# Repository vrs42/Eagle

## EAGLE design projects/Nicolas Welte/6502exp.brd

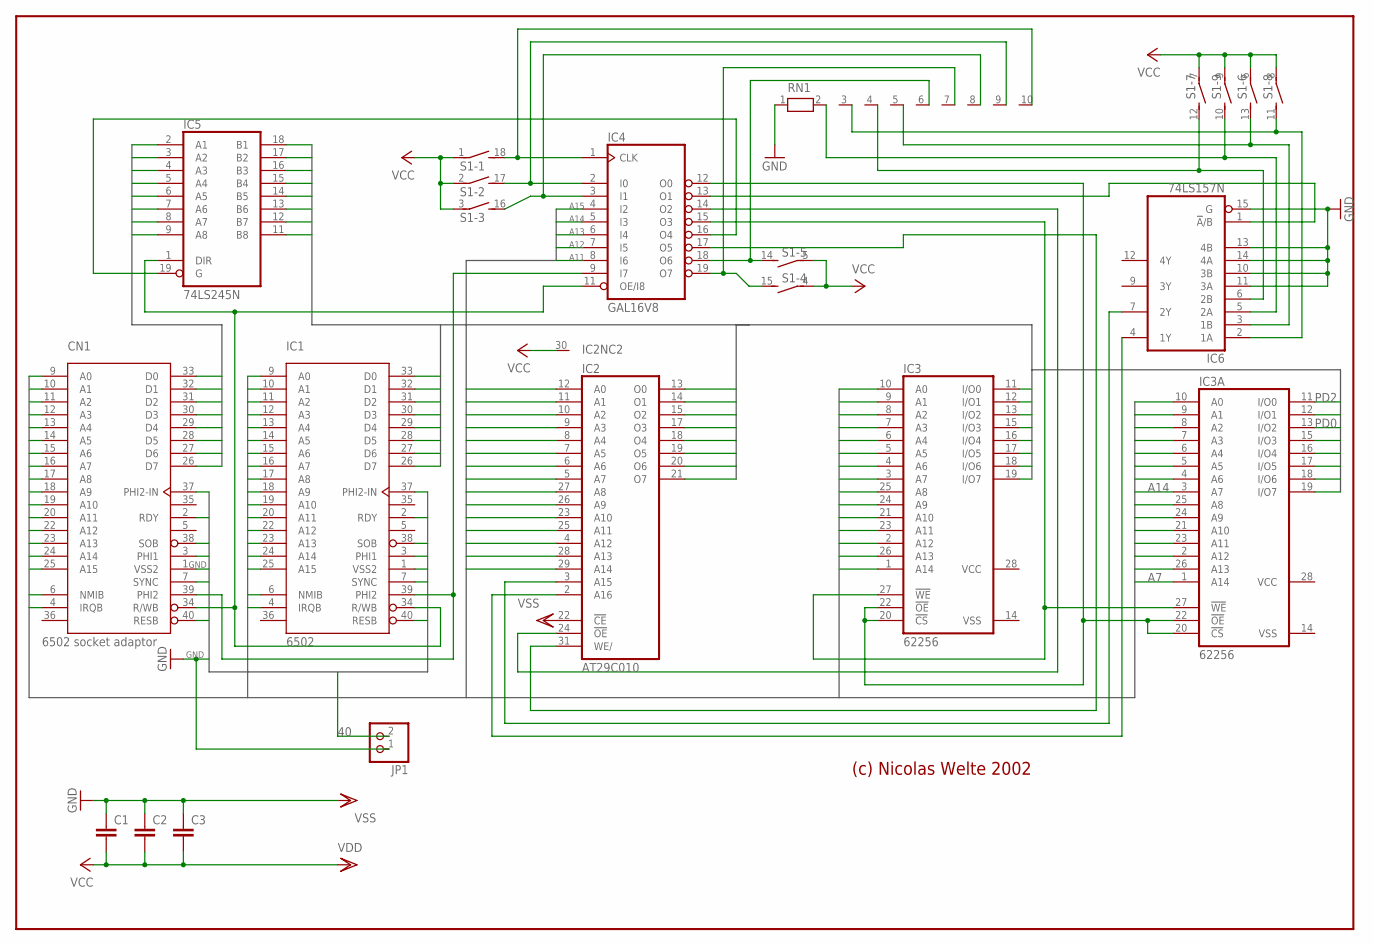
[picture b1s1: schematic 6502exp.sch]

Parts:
C1, C2, C3: C5/3; C5B3
CN1: 6502 socket adaptor; DIP-40
IC1: 6502; DIP-40
IC2: AT29C010; DIL32-3
IC3: 62256; DIL28-6
IC3A: 62256; SO28L
IC4: GAL16V8; DIL20
IC5: 74LS245N; DIL20
IC6: 74LS157N; DIL16
JP1: PINHD-1X2; 1X02
RN1: RN09; RN-10
S1: DS09E; DS-09

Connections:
2: CN1.2 (RDY), IC1.2 (RDY)
3: CN1.3 (PHI1), IC1.3 (PHI1)
7: CN1.7 (SYNC), IC1.7 (SYNC)
37: CN1.37 (PHI2-IN), IC1.37 (PHI2-IN)
38: CN1.38 (SOB), IC1.38 (SOB)
40: CN1.40 (RESB), IC1.40 (RESB), JP1.2
A0: CN1.9 (A0), IC1.9 (A0), IC2.12 (A0), IC3.10 (A0), IC3A.10 (A0)
A1: CN1.10 (A1), IC1.10 (A1), IC2.11 (A1), IC3.9 (A1), IC3A.9 (A1)
A2: CN1.11 (A2), IC1.11 (A2), IC2.10 (A2), IC3.8 (A2), IC3A.8 (A2)
A3: CN1.12 (A3), IC1.12 (A3), IC2.9 (A3), IC3.7 (A3), IC3A.7 (A3)
A4: CN1.13 (A4), IC1.13 (A4), IC2.8 (A4), IC3.6 (A4), IC3A.6 (A4)
A5: CN1.14 (A5), IC1.14 (A5), IC2.7 (A5), IC3.5 (A5), IC3A.5 (A5)
A6: CN1.15 (A6), IC1.15 (A6), IC2.6 (A6), IC3.4 (A6), IC3A.4 (A6)
A7: CN1.16 (A7), IC1.16 (A7), IC2.5 (A7), IC3.3 (A7), IC3A.1 (A14)
A8: CN1.17 (A8), IC1.17 (A8), IC2.27 (A8), IC3.25 (A8), IC3A.25 (A8)
A9: CN1.18 (A9), IC1.18 (A9), IC2.26 (A9), IC3.24 (A9), IC3A.24 (A9)
A10: CN1.19 (A10), IC1.19 (A10), IC2.23 (A10), IC3.21 (A10), IC3A.21 (A10)
A11: CN1.20 (A11), IC1.20 (A11), IC2.25 (A11), IC3.23 (A11), IC3A.23 (A11), IC4.8 (I6)
A12: CN1.22 (A12), IC1.22 (A12), IC2.4 (A12), IC3.2 (A12), IC3A.2 (A12), IC4.7 (I5)
A13: CN1.23 (A13), IC1.23 (A13), IC2.28 (A13), IC3.26 (A13), IC3A.26 (A13), IC4.6 (I4)
A14: CN1.24 (A14), IC1.24 (A14), IC2.29 (A14), IC3.1 (A14), IC3A.3 (A7), IC4.5 (I3)
A15: CN1.25 (A15), IC1.25 (A15), IC4.4 (I2)
D0: CN1.33 (D0), IC5.2 (A1)
D1: CN1.32 (D1), IC5.3 (A2)
D2: CN1.31 (D2), IC5.4 (A3)
D3: CN1.30 (D3), IC5.5 (A4)
D4: CN1.29 (D4), IC5.6 (A5)
D5: CN1.28 (D5), IC5.7 (A6)
D6: CN1.27 (D6), IC5.8 (A7)
D7: CN1.26 (D7), IC5.9 (A8)
GND: C1.1, C2.1, C3.1, CN1.1 (VSS2), CN1.21 (VSS), IC1.1 (VSS2), IC1.21 (VSS), IC2.16 (GND), IC2.22 (!CE), IC3.14 (VSS), IC3A.14 (VSS), IC4.10 (GND), IC5.10 (GND), IC6.8 (GND), IC6.10 (3B), IC6.11 (3A), IC6.13 (4B), IC6.14 (4A), IC6.15 (G), JP1.1, RN1.1
IRQ: CN1.4 (IRQB), IC1.4 (IRQB)
unnamed: CN1.34 (R/WB), IC1.34 (R/WB), IC4.11 (OE/I8), IC5.1 (DIR)
unnamed: IC4.3 (I1), RN1.8, S1.16 (2)
unnamed: CN1.39 (PHI2), IC1.39 (PHI2), IC4.9 (I7)
unnamed: IC4.2 (I0), RN1.9, S1.17 (2)
unnamed: IC4.1 (CLK), RN1.10, S1.18 (2)
unnamed: IC4.18 (O6), RN1.6, S1.14 (2)
unnamed: IC4.19 (O7), RN1.7, S1.15 (2)
unnamed: IC4.16 (O4), IC5.19 (G)
unnamed: IC3.27 (!WE), IC3A.27 (!WE), IC4.15 (O3)
unnamed: IC2.24 (!OE), IC4.14 (O2)
unnamed: IC2.31 (WE/), IC4.17 (O5)
unnamed: IC4.13 (O1), IC6.1 (!A!/B)
unnamed: IC2.3 (A15), IC6.7 (2Y)
unnamed: IC3.20 (!CS), IC3.22 (!OE), IC3A.20 (!CS), IC3A.22 (!OE), IC4.12 (O0)
unnamed: IC2.2 (A16), IC6.4 (1Y)
unnamed: IC6.2 (1A), RN1.3, S1.11 (2)
unnamed: IC6.3 (1B), RN1.5, S1.13 (2)
unnamed: IC6.5 (2A), RN1.2, S1.10 (2)
unnamed: IC6.6 (2B), RN1.4, S1.12 (2)
NMI: CN1.6 (NMIB), IC1.6 (NMIB)
PD0: IC1.33 (D0), IC2.13 (O0), IC3.11 (I/O0), IC3A.13 (I/O2), IC5.18 (B1)
PD1: IC1.32 (D1), IC2.14 (O1), IC3.12 (I/O1), IC3A.12 (I/O1), IC5.17 (B2)
PD2: IC1.31 (D2), IC2.15 (O2), IC3.13 (I/O2), IC3A.11 (I/O0), IC5.16 (B3)
PD3: IC1.30 (D3), IC2.17 (O3), IC3.15 (I/O3), IC3A.15 (I/O3), IC5.15 (B4)
PD4: IC1.29 (D4), IC2.18 (O4), IC3.16 (I/O4), IC3A.16 (I/O4), IC5.14 (B5)
PD5: IC1.28 (D5), IC2.19 (O5), IC3.17 (I/O5), IC3A.17 (I/O5), IC5.13 (B6)
PD6: IC1.27 (D6), IC2.20 (O6), IC3.18 (I/O6), IC3A.18 (I/O6), IC5.12 (B7)
PD7: IC1.26 (D7), IC2.21 (O7), IC3.19 (I/O7), IC3A.19 (I/O7), IC5.11 (B8)
VCC: C1.2, C2.2, C3.2, CN1.8 (VDD), IC1.8 (VDD), IC2.30 (NC), IC2.32 (VCC), IC3.28 (VCC), IC3A.28 (VCC), IC4.20 (VCC), IC5.20 (VCC), IC6.16 (VCC), S1.1, S1.2 (1), S1.3 (1), S1.4 (1), S1.5 (1), S1.6 (1), S1.7 (1), S1.8 (1), S1.9 (1)

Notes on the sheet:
(c) Nicolas Welte 2002

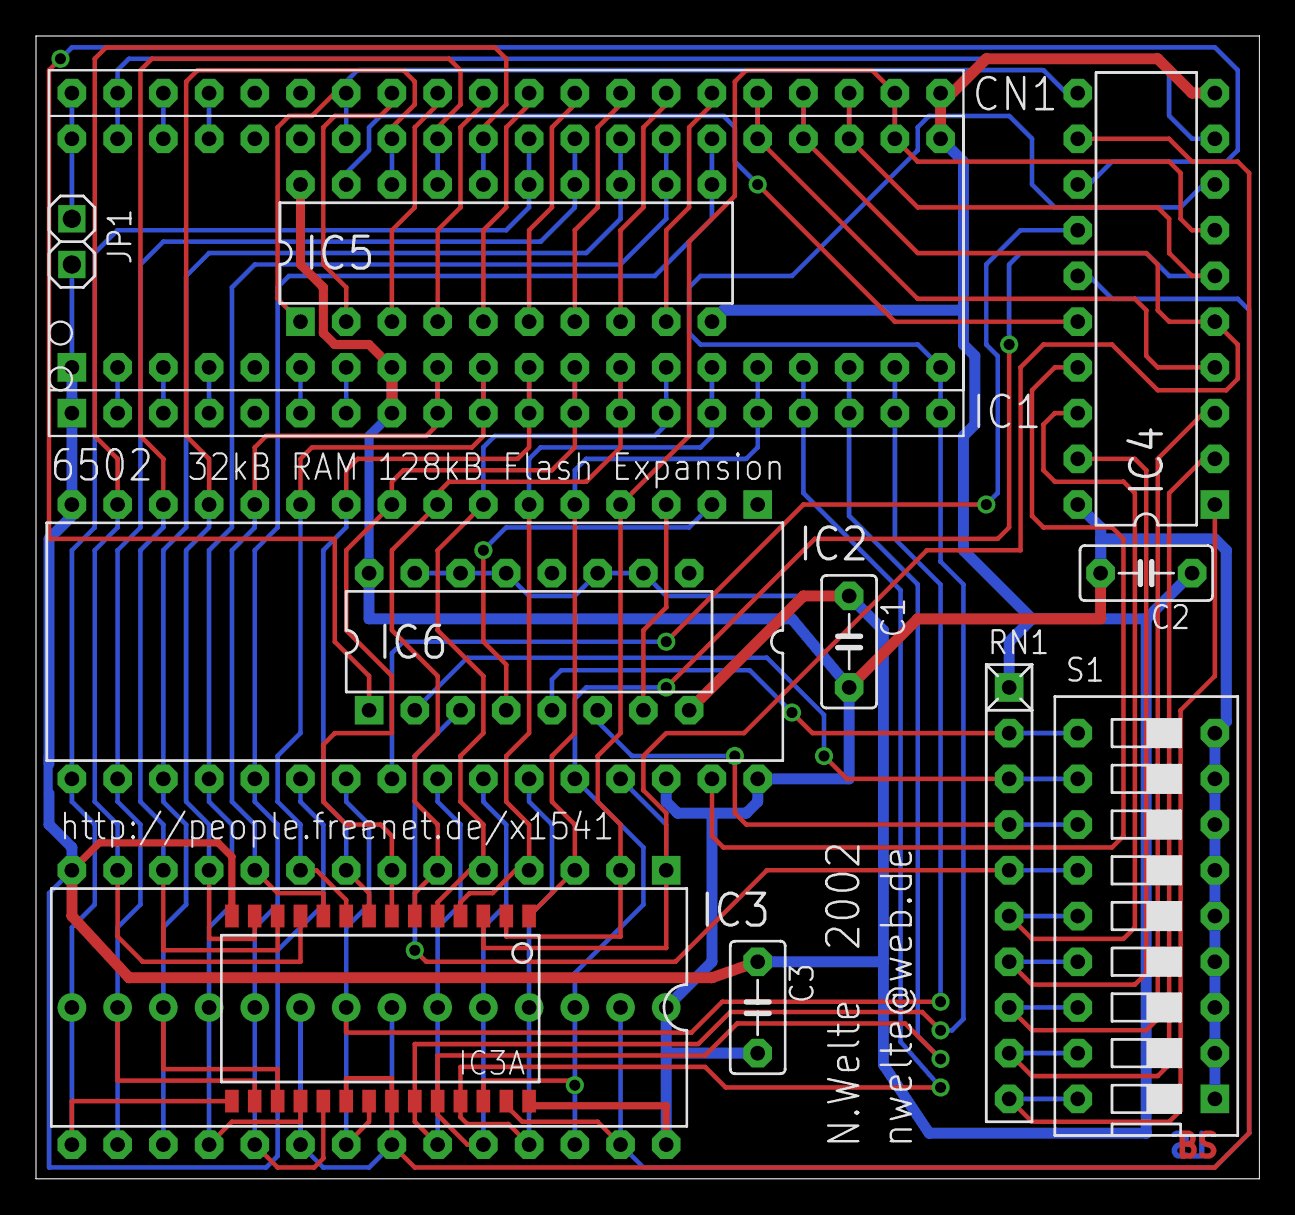
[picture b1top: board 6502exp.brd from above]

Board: 2 copper layers, 68.0 x 63.5 mm, 14 parts (0 on the bottom side), 61 nets.

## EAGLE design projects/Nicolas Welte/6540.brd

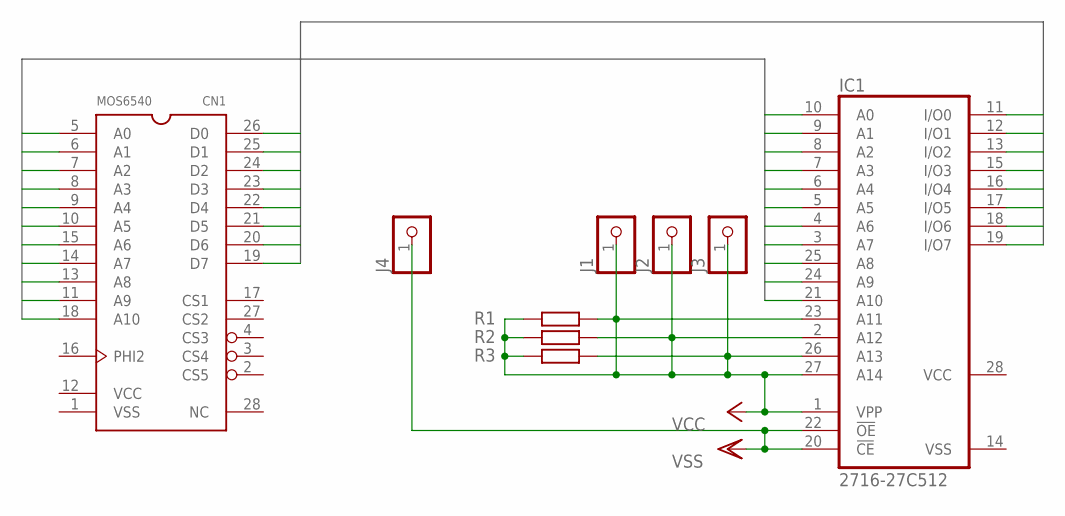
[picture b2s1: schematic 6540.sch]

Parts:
CN1: MOS6540; DIP-28
IC1: 2716-27C512; DIL28-6
J1, J2, J3, J4: PINHD-1X1; 1X01
R1, R2, R3: R-EU_M0805; M0805

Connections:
A0: CN1.5 (A0), IC1.10 (A0)
A1: CN1.6 (A1), IC1.9 (A1)
A2: CN1.7 (A2), IC1.8 (A2)
A3: CN1.8 (A3), IC1.7 (A3)
A4: CN1.9 (A4), IC1.6 (A4)
A5: CN1.10 (A5), IC1.5 (A5)
A6: CN1.15 (A6), IC1.4 (A6)
A7: CN1.14 (A7), IC1.3 (A7)
A8: CN1.13 (A8), IC1.25 (A8)
A9: CN1.11 (A9), IC1.24 (A9)
A10: CN1.18 (A10), IC1.21 (A10)
D0: CN1.26 (D0), IC1.11 (I/O0)
D1: CN1.25 (D1), IC1.12 (I/O1)
D2: CN1.24 (D2), IC1.13 (I/O2)
D3: CN1.23 (D3), IC1.15 (I/O3)
D4: CN1.22 (D4), IC1.16 (I/O4)
D5: CN1.21 (D5), IC1.17 (I/O5)
D6: CN1.20 (D6), IC1.18 (I/O6)
D7: CN1.19 (D7), IC1.19 (I/O7)
VCC: CN1.12 (VCC), IC1.1 (VPP), IC1.2 (A12), IC1.23 (A11), IC1.26 (A13), IC1.27 (A14), IC1.28 (VCC), J1.1, J2.1, J3.1, R1.1, R1.2, R2.1, R2.2, R3.1, R3.2
VSS: CN1.1 (VSS), IC1.14 (VSS), IC1.20 (!CE), IC1.22 (!OE), J4.1

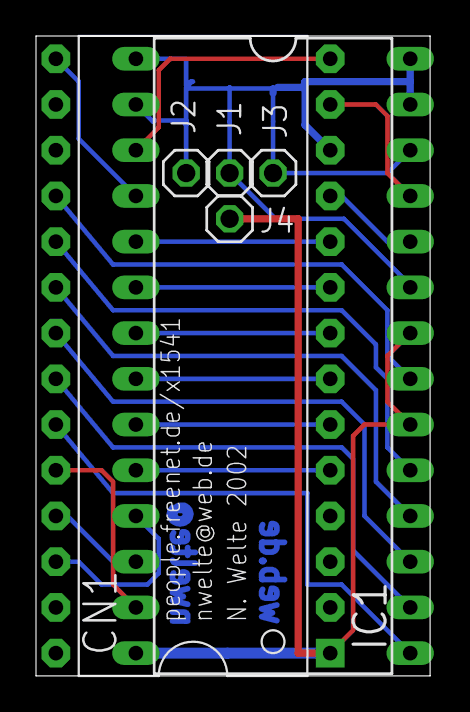
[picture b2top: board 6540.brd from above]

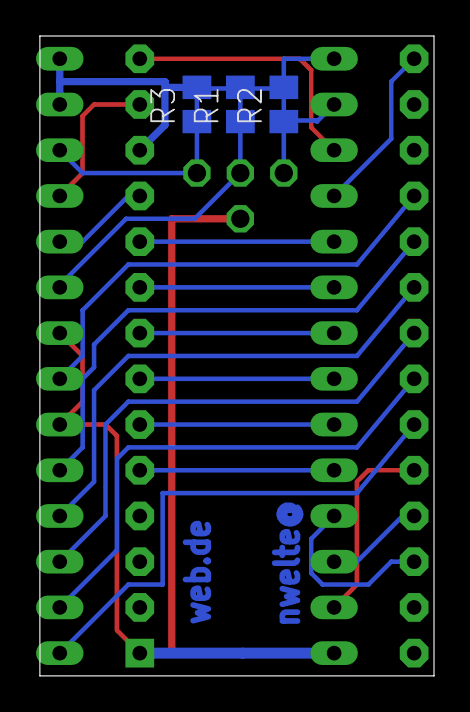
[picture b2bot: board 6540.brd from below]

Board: 2 copper layers, 21.9 x 35.5 mm, 9 parts (3 on the bottom side), 21 nets.

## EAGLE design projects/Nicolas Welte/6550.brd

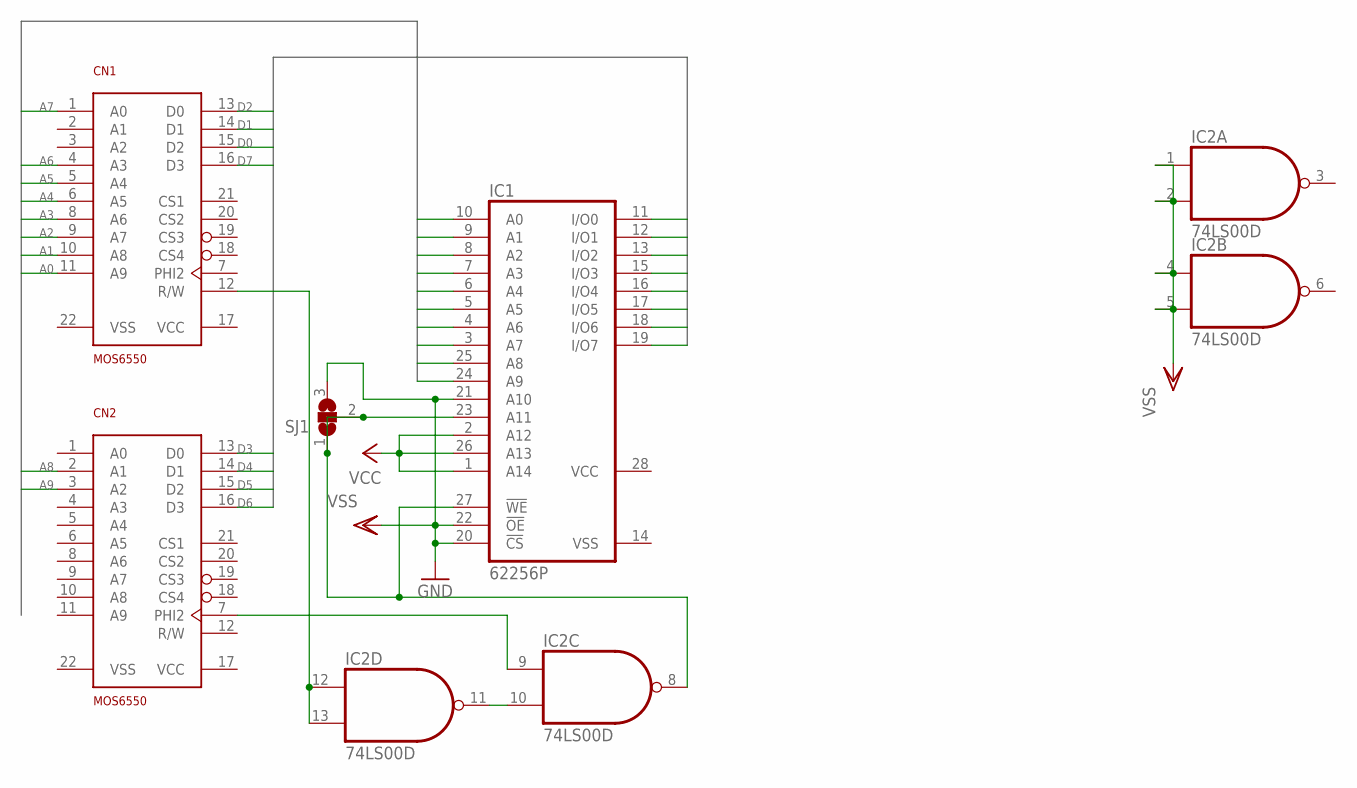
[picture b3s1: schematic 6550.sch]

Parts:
CN1, CN2: MOS6550; DIP-22
IC1: 62256P; DIL28-6
IC2: 74LS00D; SO14
SJ1: SJ2W; SJ_2

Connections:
A0: CN1.11 (A9), IC1.10 (A0)
A1: CN1.10 (A8), IC1.9 (A1)
A2: CN1.9 (A7), IC1.8 (A2)
A3: CN1.8 (A6), IC1.7 (A3)
A4: CN1.6 (A5), IC1.6 (A4)
A5: CN1.5 (A4), IC1.5 (A5)
A6: CN1.4 (A3), IC1.4 (A6)
A7: CN1.1 (A0), IC1.3 (A7)
A8: CN2.2 (A1), IC1.25 (A8)
A9: CN2.3 (A2), IC1.24 (A9)
D0: CN1.15 (D2), IC1.11 (I/O0)
D1: CN1.14 (D1), IC1.12 (I/O1)
D2: CN1.13 (D0), IC1.13 (I/O2)
D3: CN2.13 (D0), IC1.15 (I/O3)
D4: CN2.14 (D1), IC1.16 (I/O4)
D5: CN2.15 (D2), IC1.17 (I/O5)
D6: CN2.16 (D3), IC1.18 (I/O6)
D7: CN1.16 (D3), IC1.19 (I/O7)
unnamed: CN1.12 (R/W), IC2.12 (I0), IC2.13 (I1)
unnamed: IC2.10 (I1), IC2.11 (O)
unnamed: CN2.7 (PHI2), IC2.9 (I0)
unnamed: IC1.23 (A11), IC1.27 (!WE), IC2.8 (O), SJ1.1, SJ1.2
VCC: CN1.17 (VCC), CN2.17 (VCC), IC1.1 (A14), IC1.2 (A12), IC1.26 (A13), IC1.28 (VCC), IC2.14 (VCC)
VSS: CN1.22 (VSS), CN2.22 (VSS), IC1.14 (VSS), IC1.20 (!CS), IC1.21 (A10), IC1.22 (!OE), IC2.1 (I0), IC2.2 (I1), IC2.4 (I0), IC2.5 (I1), IC2.7 (GND), SJ1.3

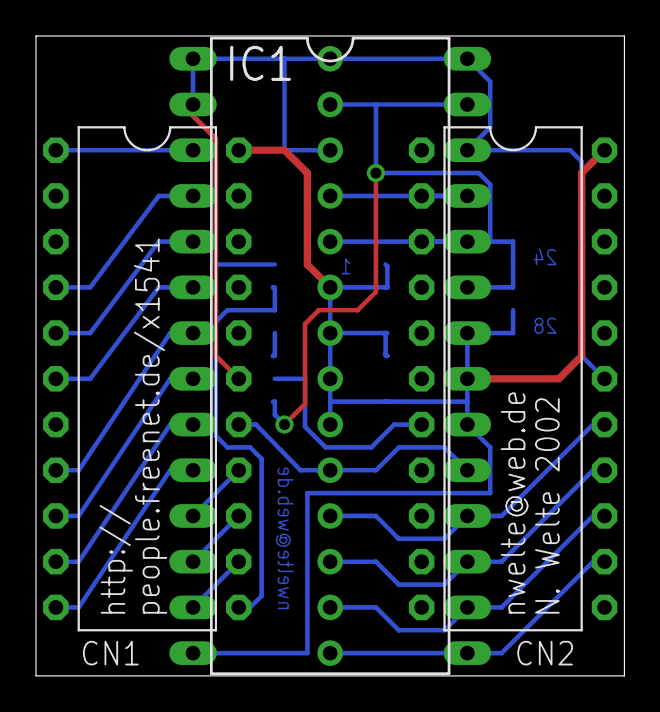
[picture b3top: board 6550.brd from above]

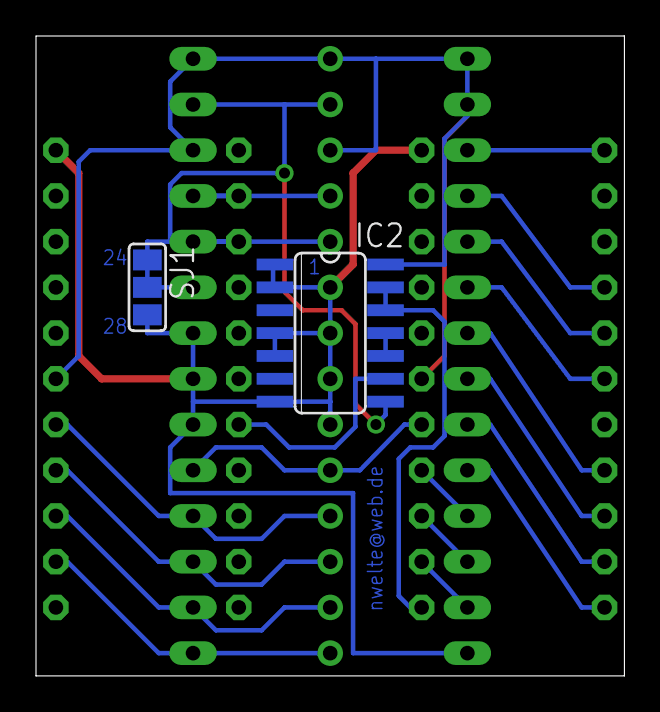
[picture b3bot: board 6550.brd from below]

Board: 2 copper layers, 32.7 x 35.5 mm, 5 parts (2 on the bottom side), 24 nets.

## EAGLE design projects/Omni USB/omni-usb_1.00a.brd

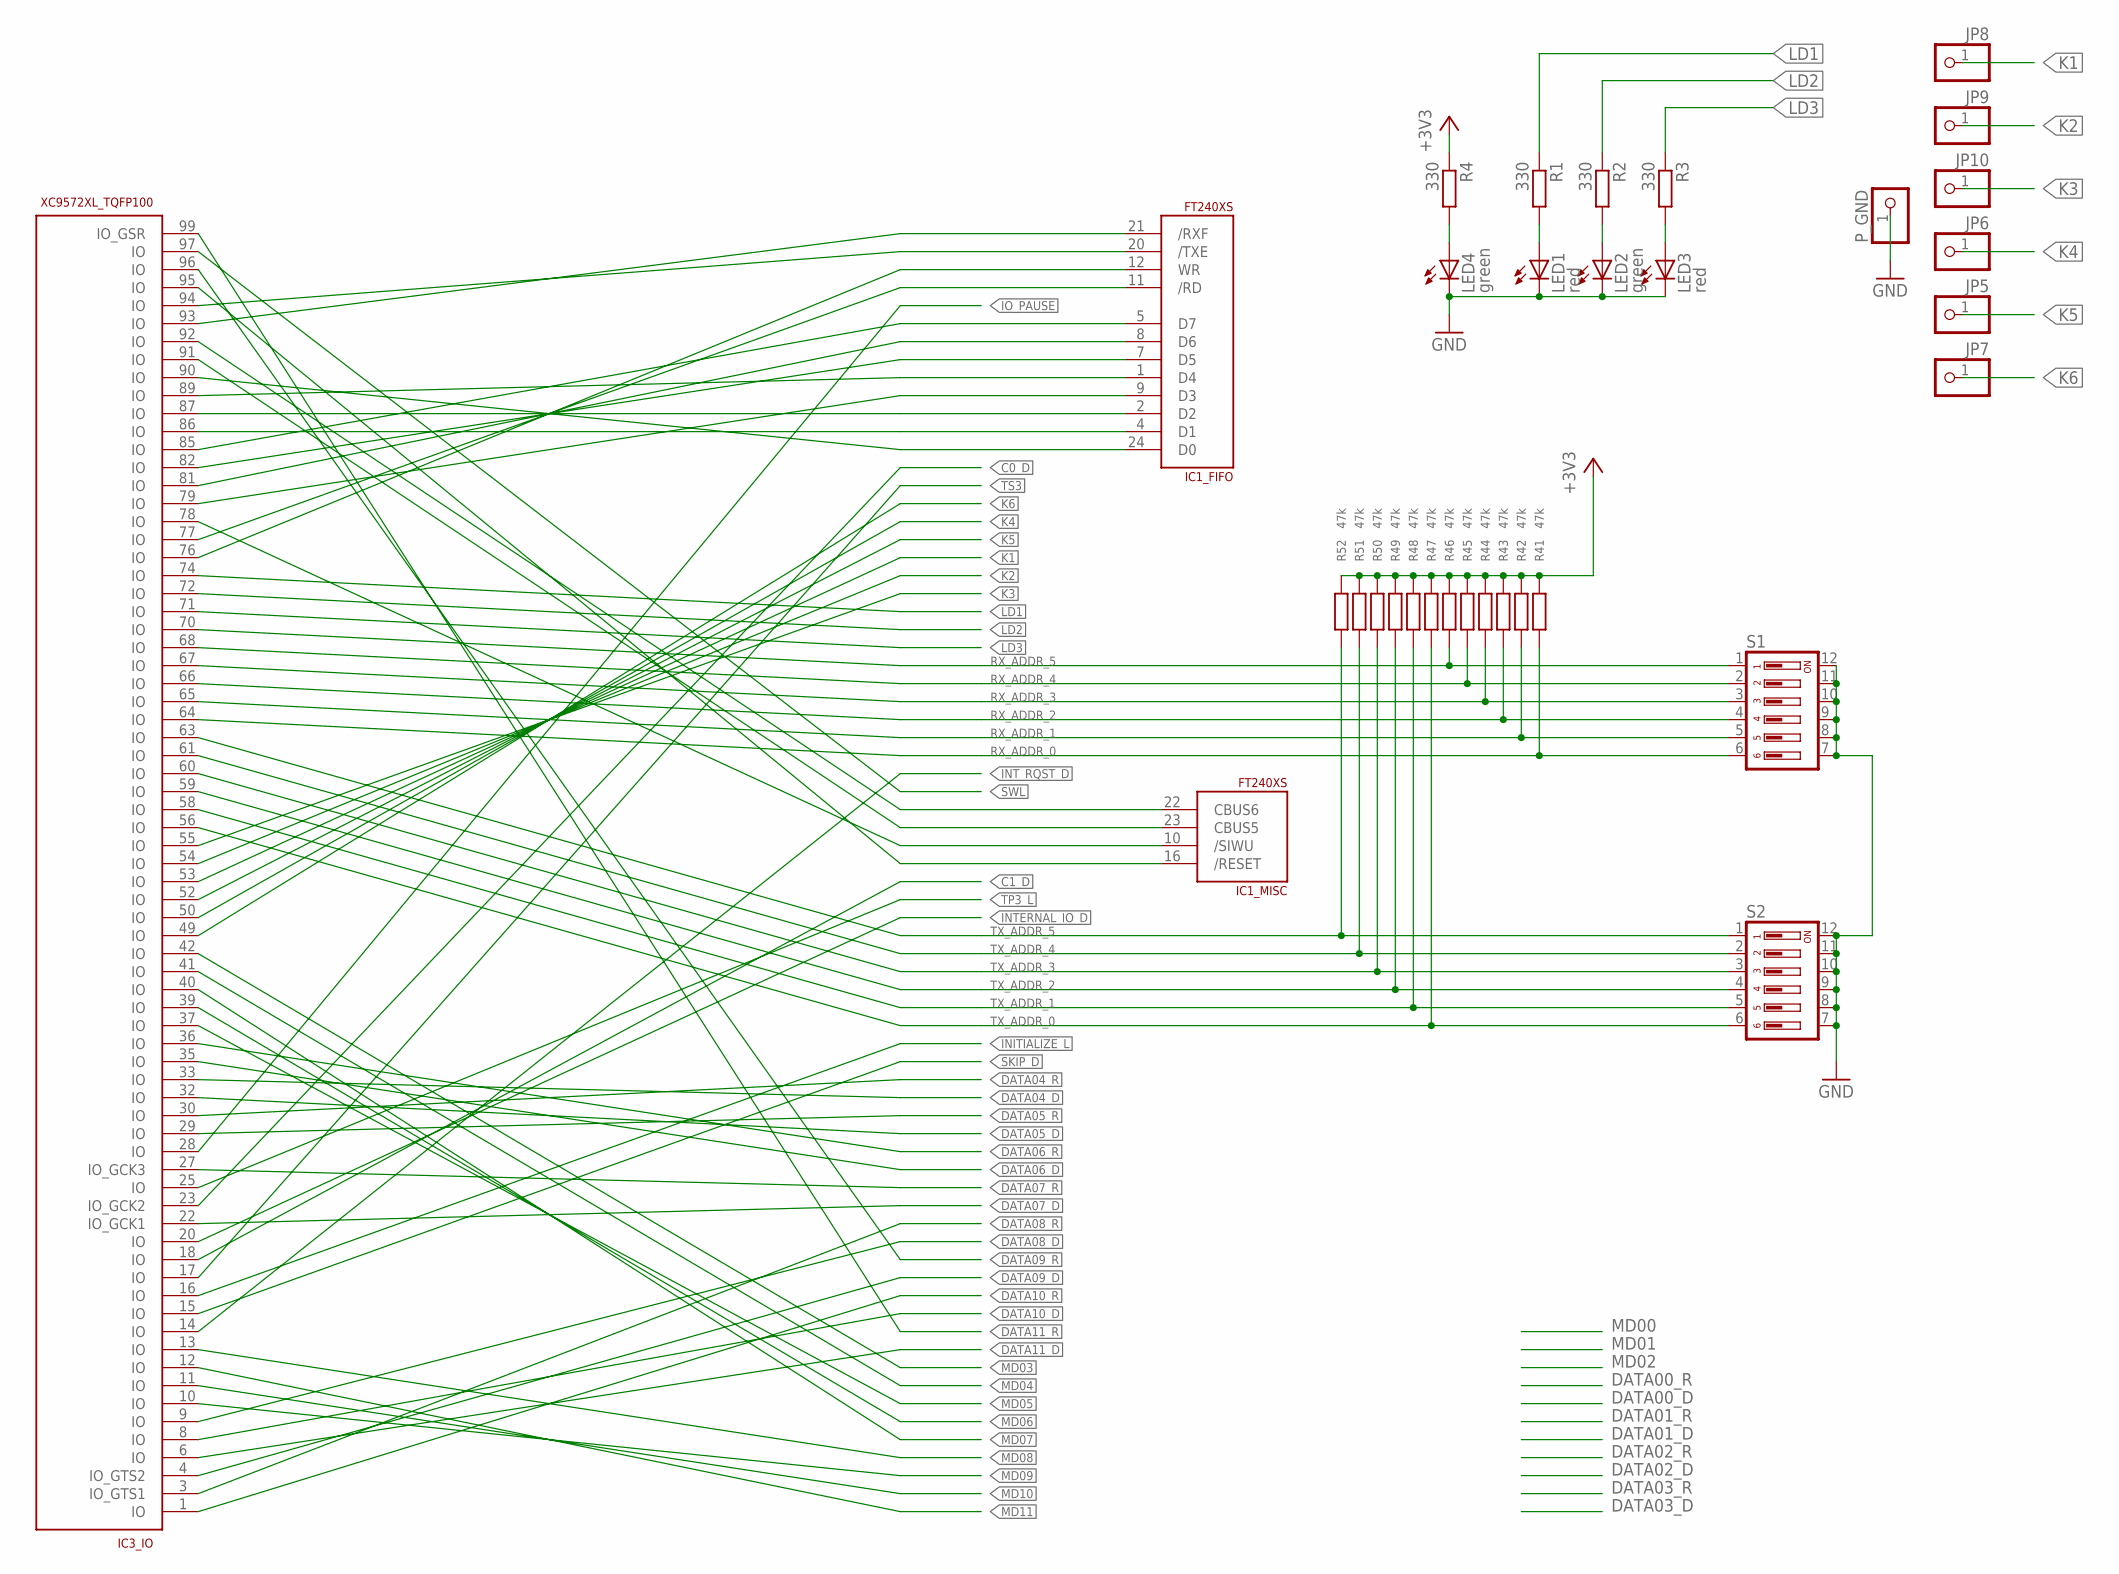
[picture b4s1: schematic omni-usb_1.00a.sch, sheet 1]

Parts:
IC1: FT240XS; TSSOP24; MPN FT240XS
IC3: XC9572XL_TQFP100; TQ100; MPN XC9572XL-10TQG100C
JP5, JP6, JP7, JP8, JP9, JP10: PINHD-1X1; 1X01
LED1, LED3: red; CHIPLED_0805; MPN KP-2012SRC-PRV
LED2, LED4: green; CHIPLED_0805; MPN KPT-2012CGCK
P_GND: PINHD-1X1; 1X01
R1, R2, R3, R4: 330; R0805
R41, R42, R43, R44, R45, R46, R47, R48, R49, R50, R51, R52: 47k; R0805; MPN ERJ6GEYJ473V
S1, S2: DIP06YL

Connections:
!RD: IC1.11 (/RD), IC3.77 (IO)
!RESET: IC1.16 (/RESET), IC3.95 (IO)
!RXF: IC1.21 (/RXF), IC3.93 (IO)
!TXE: IC1.20 (/TXE), IC3.94 (IO)
+3V3: R4.1, R41.2, R42.2, R43.2, R44.2, R45.2, R46.2, R47.2, R48.2, R49.2, R50.2, R51.2, R52.2; also elsewhere on the board
/SIWU: IC1.10 (/SIWU), IC3.78 (IO)
C0_D: IC3.23 (IO_GCK2); also elsewhere on the board
C1_D: IC3.18 (IO); also elsewhere on the board
CBUS5: IC1.23 (CBUS5), IC3.91 (IO)
CBUS6: IC1.22 (CBUS6), IC3.92 (IO)
D0: IC1.24 (D0), IC3.90 (IO)
D1: IC1.4 (D1), IC3.86 (IO)
D2: IC1.2 (D2), IC3.87 (IO)
D3: IC1.9 (D3), IC3.79 (IO)
D4: IC1.1 (D4), IC3.89 (IO)
D5: IC1.7 (D5), IC3.82 (IO)
D6: IC1.8 (D6), IC3.81 (IO)
D7: IC1.5 (D7), IC3.85 (IO)
DATA04_D: IC3.33 (IO); also elsewhere on the board
DATA04_R: IC3.30 (IO); also elsewhere on the board
DATA05_D: IC3.32 (IO); also elsewhere on the board
DATA05_R: IC3.29 (IO); also elsewhere on the board
DATA06_D: IC3.35 (IO); also elsewhere on the board
DATA06_R: IC3.36 (IO); also elsewhere on the board
DATA07_D: IC3.22 (IO_GCK1); also elsewhere on the board
DATA07_R: IC3.27 (IO_GCK3); also elsewhere on the board
DATA08_D: IC3.9 (IO); also elsewhere on the board
DATA08_R: IC3.3 (IO_GTS1); also elsewhere on the board
DATA09_D: IC3.4 (IO_GTS2); also elsewhere on the board
DATA09_R: IC3.96 (IO); also elsewhere on the board
DATA10_D: IC3.8 (IO); also elsewhere on the board
DATA10_R: IC3.1 (IO); also elsewhere on the board
DATA11_D: IC3.6 (IO); also elsewhere on the board
DATA11_R: IC3.99 (IO_GSR); also elsewhere on the board
GND: LED1.C, LED2.C, LED3.C, LED4.C, P_GND.1, S1.7, S1.8, S1.9, S1.10, S1.11, S1.12, S2.7, S2.8, S2.9, S2.10, S2.11, S2.12; also elsewhere on the board
INITIALIZE_L: IC3.16 (IO); also elsewhere on the board
INTERNAL_IO_D: IC3.20 (IO); also elsewhere on the board
INT_RQST_D: IC3.14 (IO); also elsewhere on the board
IO_PAUSE: IC3.28 (IO); also elsewhere on the board
K1: IC3.53 (IO), JP8.1
K2: IC3.54 (IO), JP9.1
K3: IC3.55 (IO), JP10.1
K4: IC3.50 (IO), JP6.1
K5: IC3.52 (IO), JP5.1
K6: IC3.49 (IO), JP7.1
LD1: IC3.74 (IO), R1.1
LD2: IC3.72 (IO), R2.1
LD3: IC3.71 (IO), R3.1
LED3: LED2.A, R2.2
MD03: IC3.42 (IO); also elsewhere on the board
MD04: IC3.41 (IO); also elsewhere on the board
MD05: IC3.37 (IO); also elsewhere on the board
MD06: IC3.39 (IO); also elsewhere on the board
MD07: IC3.40 (IO); also elsewhere on the board
MD08: IC3.13 (IO); also elsewhere on the board
MD09: IC3.10 (IO); also elsewhere on the board
MD10: IC3.11 (IO); also elsewhere on the board
MD11: IC3.12 (IO); also elsewhere on the board
unnamed: IC1.12 (WR), IC3.76 (IO)
unnamed: LED1.A, R1.2
unnamed: LED4.A, R4.2
unnamed: LED3.A, R3.2
RX_ADDR_0: IC3.64 (IO), R41.1, S1.6
RX_ADDR_1: IC3.65 (IO), R42.1, S1.5
RX_ADDR_2: IC3.66 (IO), R43.1, S1.4
RX_ADDR_3: IC3.67 (IO), R44.1, S1.3
RX_ADDR_4: IC3.68 (IO), R45.1, S1.2
RX_ADDR_5: IC3.70 (IO), R46.1, S1.1
SKIP_D: IC3.15 (IO); also elsewhere on the board
SWL: IC3.97 (IO); also elsewhere on the board
TP3_L: IC3.25 (IO); also elsewhere on the board
TS3: IC3.17 (IO); also elsewhere on the board
TX_ADDR_0: IC3.56 (IO), R47.1, S2.6
TX_ADDR_1: IC3.58 (IO), R48.1, S2.5
TX_ADDR_2: IC3.59 (IO), R49.1, S2.4
TX_ADDR_3: IC3.60 (IO), R50.1, S2.3
TX_ADDR_4: IC3.61 (IO), R51.1, S2.2
TX_ADDR_5: IC3.63 (IO), R52.1, S2.1

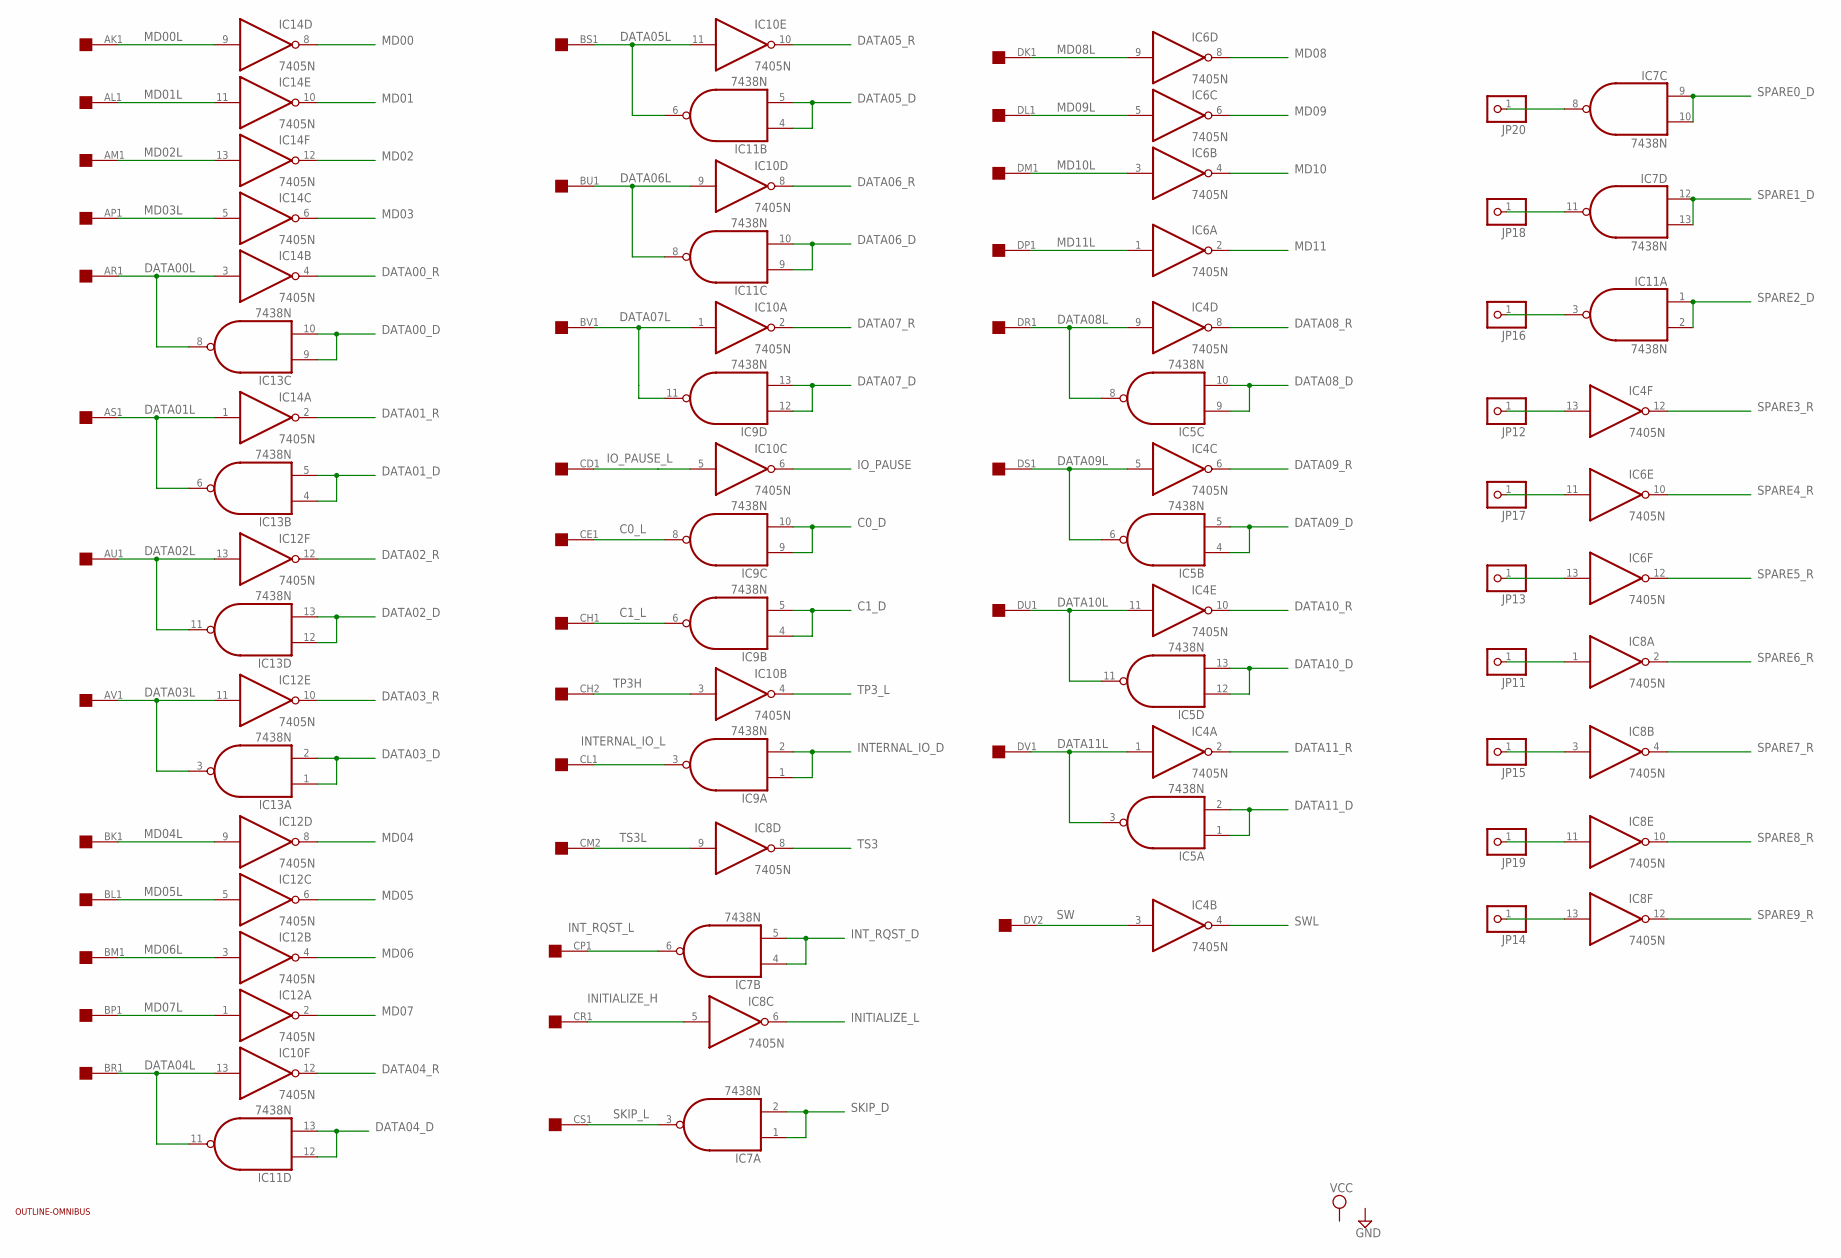
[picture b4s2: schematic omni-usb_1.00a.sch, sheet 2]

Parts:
IC4, IC6, IC8, IC10, IC12, IC14: 7405N; DIL14; MPN SN74AHC05N
IC5, IC7, IC9, IC11, IC13: 7438N; DIL14; MPN SN7438N
JP11, JP12, JP13, JP14, JP15, JP16, JP17, JP18, JP19, JP20: PINHD-1X1; 1X01
U$1: OUTLINE-OMNIBUS; OMNIBUS
U$2: QUAD; EDGE-CON8

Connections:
C0_D: IC9.9 (I0), IC9.10 (I1); also elsewhere on the board
C0_L: IC9.8 (O), U$2.CE1
C1_D: IC9.4 (I0), IC9.5 (I1); also elsewhere on the board
C1_L: IC9.6 (O), U$2.CH1
DATA00L: IC13.8 (O), IC14.3 (I), U$2.AR1
DATA00_D: IC13.9 (I0), IC13.10 (I1)
DATA00_R: IC14.4 (O); also elsewhere on the board
DATA01L: IC13.6 (O), IC14.1 (I), U$2.AS1
DATA01_D: IC13.4 (I0), IC13.5 (I1)
DATA01_R: IC14.2 (O); also elsewhere on the board
DATA02L: IC12.13 (I), IC13.11 (O), U$2.AU1
DATA02_D: IC13.12 (I0), IC13.13 (I1)
DATA02_R: IC12.12 (O); also elsewhere on the board
DATA03L: IC12.11 (I), IC13.3 (O), U$2.AV1
DATA03_D: IC13.1 (I0), IC13.2 (I1)
DATA03_R: IC12.10 (O); also elsewhere on the board
DATA04L: IC10.13 (I), IC11.11 (O), U$2.BR1
DATA04_D: IC11.12 (I0), IC11.13 (I1); also elsewhere on the board
DATA04_R: IC10.12 (O); also elsewhere on the board
DATA05L: IC10.11 (I), IC11.6 (O), U$2.BS1
DATA05_D: IC11.4 (I0), IC11.5 (I1); also elsewhere on the board
DATA05_R: IC10.10 (O); also elsewhere on the board
DATA06L: IC10.9 (I), IC11.8 (O), U$2.BU1
DATA06_D: IC11.9 (I0), IC11.10 (I1); also elsewhere on the board
DATA06_R: IC10.8 (O); also elsewhere on the board
DATA07L: IC9.11 (O), IC10.1 (I), U$2.BV1
DATA07_D: IC9.12 (I0), IC9.13 (I1); also elsewhere on the board
DATA07_R: IC10.2 (O); also elsewhere on the board
DATA08L: IC4.9 (I), IC5.8 (O), U$2.DR1
DATA08_D: IC5.9 (I0), IC5.10 (I1); also elsewhere on the board
DATA08_R: IC4.8 (O); also elsewhere on the board
DATA09L: IC4.5 (I), IC5.6 (O), U$2.DS1
DATA09_D: IC5.4 (I0), IC5.5 (I1); also elsewhere on the board
DATA09_R: IC4.6 (O); also elsewhere on the board
DATA10L: IC4.11 (I), IC5.11 (O), U$2.DU1
DATA10_D: IC5.12 (I0), IC5.13 (I1); also elsewhere on the board
DATA10_R: IC4.10 (O); also elsewhere on the board
DATA11L: IC4.1 (I), IC5.3 (O), U$2.DV1
DATA11_D: IC5.1 (I0), IC5.2 (I1); also elsewhere on the board
DATA11_R: IC4.2 (O); also elsewhere on the board
GND: IC4.7 (GND), IC5.7 (GND), IC6.7 (GND), IC7.7 (GND), IC8.7 (GND), IC9.7 (GND), IC10.7 (GND), IC11.7 (GND), IC12.7 (GND), IC13.7 (GND), IC14.7 (GND); also elsewhere on the board
INITIALIZE_H: IC8.5 (I), U$2.CR1
INITIALIZE_L: IC8.6 (O); also elsewhere on the board
INTERNAL_IO_D: IC9.1 (I0), IC9.2 (I1); also elsewhere on the board
INTERNAL_IO_L: IC9.3 (O), U$2.CL1
INT_RQST_D: IC7.4 (I0), IC7.5 (I1); also elsewhere on the board
INT_RQST_L: IC7.6 (O), U$2.CP1
IO_PAUSE: IC10.6 (O); also elsewhere on the board
IO_PAUSE_L: IC10.5 (I), U$2.CD1
MD00: IC14.8 (O); also elsewhere on the board
MD00L: IC14.9 (I), U$2.AK1
MD01: IC14.10 (O); also elsewhere on the board
MD01L: IC14.11 (I), U$2.AL1
MD02: IC14.12 (O); also elsewhere on the board
MD02L: IC14.13 (I), U$2.AM1
MD03: IC14.6 (O); also elsewhere on the board
MD03L: IC14.5 (I), U$2.AP1
MD04: IC12.8 (O); also elsewhere on the board
MD04L: IC12.9 (I), U$2.BK1
MD05: IC12.6 (O); also elsewhere on the board
MD05L: IC12.5 (I), U$2.BL1
MD06: IC12.4 (O); also elsewhere on the board
MD06L: IC12.3 (I), U$2.BM1
MD07: IC12.2 (O); also elsewhere on the board
MD07L: IC12.1 (I), U$2.BP1
MD08: IC6.8 (O); also elsewhere on the board
MD08L: IC6.9 (I), U$2.DK1
MD09: IC6.6 (O); also elsewhere on the board
MD09L: IC6.5 (I), U$2.DL1
MD10: IC6.4 (O); also elsewhere on the board
MD10L: IC6.3 (I), U$2.DM1
MD11: IC6.2 (O); also elsewhere on the board
MD11L: IC6.1 (I), U$2.DP1
unnamed: IC7.8 (O), JP20.1
unnamed: IC7.11 (O), JP18.1
unnamed: IC11.3 (O), JP16.1
unnamed: IC4.13 (I), JP12.1
unnamed: IC6.11 (I), JP17.1
unnamed: IC6.13 (I), JP13.1
unnamed: IC8.1 (I), JP11.1
unnamed: IC8.3 (I), JP15.1
unnamed: IC8.11 (I), JP19.1
unnamed: IC8.13 (I), JP14.1
SKIP_D: IC7.1 (I0), IC7.2 (I1); also elsewhere on the board
SKIP_L: IC7.3 (O), U$2.CS1
SPARE0_D: IC7.9 (I0), IC7.10 (I1)
SPARE1_D: IC7.12 (I0), IC7.13 (I1)
SPARE2_D: IC11.1 (I0), IC11.2 (I1)
SPARE3_R: IC4.12 (O); also elsewhere on the board
SPARE4_R: IC6.10 (O); also elsewhere on the board
SPARE5_R: IC6.12 (O); also elsewhere on the board
SPARE6_R: IC8.2 (O); also elsewhere on the board
SPARE7_R: IC8.4 (O); also elsewhere on the board
SPARE8_R: IC8.10 (O); also elsewhere on the board
SPARE9_R: IC8.12 (O); also elsewhere on the board
SW: IC4.3 (I), U$2.DV2
SWL: IC4.4 (O); also elsewhere on the board
TP3H: IC10.3 (I), U$2.CH2
TP3_L: IC10.4 (O); also elsewhere on the board
TS3: IC8.8 (O); also elsewhere on the board
TS3L: IC8.9 (I), U$2.CM2
VCC: IC4.14 (VCC), IC5.14 (VCC), IC6.14 (VCC), IC7.14 (VCC), IC8.14 (VCC), IC9.14 (VCC), IC10.14 (VCC), IC11.14 (VCC), IC12.14 (VCC), IC13.14 (VCC), IC14.14 (VCC); also elsewhere on the board

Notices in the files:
projects/Omni USB/omni-usb_1.00a.brd:
(C) 2013 Ph. Hachtmann
parts and their libraries:
frames: (C) 2013 Philipp Hachtmann
